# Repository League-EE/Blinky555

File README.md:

# League-EE-Blinky555

## Summary 

This project creates a circuit board with a flashing LED using a 555 timer IC.

This project spans for several sessions and will teach:

* Ohms Law and basic electronics
* How the 555 timer works
* Creating a schematic with Eagle
* Creating a printed circuit board with Eagle
* Soldering skills

## Eagle

See the section on [Eagle](Eagle/) for details.

## Lesson Plan

The [Lesson Plan](Lesson%20Plan/) folder has the formatted lesson plan

## LTspice

LTspice is a circuit simulator and can be incorporated into a future lesson. Simulation
files for the Blinky555 circuit are in the [LTSpice](LTSpice/) folder.

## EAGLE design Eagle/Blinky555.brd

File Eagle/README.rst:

*********************
League-EE-Blinky555
*********************

.. contents:: Table of Contents

Summary 
=========

These are the Eagle CAD files for the  555 timer, including schematic, board layout, and *most importantly, a custom Eagle library* so you don't have to go searching through thousands of parts.

.. figure:: Blinky555.png

Installation
====================

Install the Library
---------------------

This was the most confusing part. Eagle does not make it obvious at all how to add a library.

**(This needs to be updated!)**

1. Copy the *League_555_Blinky.lbr* file to the *lbr/* directory
2. Go to Library Manager and ???
3. Click on [Browse] button and navigate to the *League_555_Blinky.lbr* file
4. Click on Open

Copy the Project Files (Optional)
-----------------------------------

Create a folder where Eagle projects are stored. This is usually a different folder from the
program files.

Copy the .sch (schematic) and .brd (board file) into the new folder.

Laying Out
===========

Warning: Either the stop mask must be opened up underneath the coin cell or a solder blob
placed on the bottom pad to contact the bottom of the coin cell.

The example file includes a ground filled polygon.

Example Circuit
=================

**(Circuit not tested; the values were guessed at. Needs need updating.)**

.. figure:: Blinky555-schem.png

BOM (Bill of Materials)
========================

* Resistor, ?k, 0805, 2 pcs
* Capacitor, ?uF, 0805, 1 pc
* LED, 5 mm
* Timer IC, LM555
* Coin cell

  * CR1220 -- 12 mm diameter, 2 mm thick
  * CR2032 -- 20 mm diameter, 3.2 mm thick
  
* Coin cell holder, to match coin cell

  * CR1220 type -- Keystone, 3000
  * CR2032 type -- Linx Technologies, 712-BAT-HLD-001 

Recommended Reference Tutorials
================================

(Add links to best Eagle tutorials on the web; good for both instructors and kids as a reference.)

Ideas for Improvements
======================
* **Update the actual component values before ordering parts!**
* Add a potentiometer so the kids can adjust the blink rate
* Consider a speaker output and make this an oscillator/tone generator

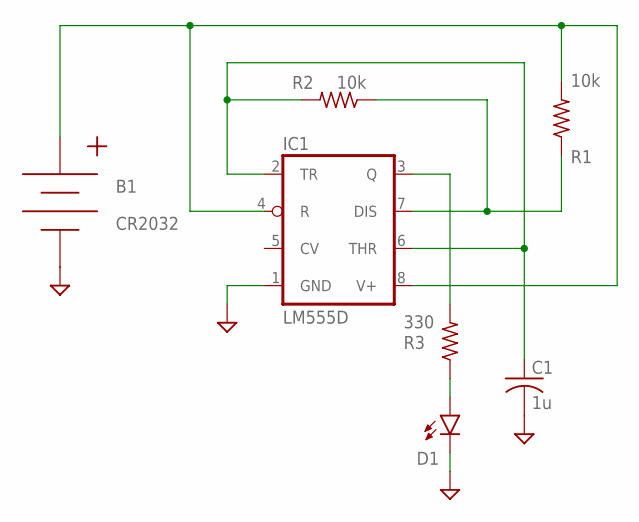
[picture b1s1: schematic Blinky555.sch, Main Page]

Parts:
B1: CR2032; BATTCON_20MM_4LEGS
C1: 1u; C0805
D1: LED; LED_5MM
IC1: LM555D; SO08
R1, R2: 10k; R0805
R3: 330; R0805

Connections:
+: B1.POSITIVE@1 (+), B1.POSITIVE@2 (+), B1.POSITIVE@3 (+), B1.POSITIVE@4 (+), IC1.4 (R), IC1.8 (V+), R1.2
GND: B1.NEGATIVE (-), C1.2, D1.K (C), IC1.1 (GND)
unnamed: IC1.7 (DIS), R1.1, R2.1
unnamed: C1.1, IC1.2 (TR), IC1.6 (THR), R2.2
unnamed: D1.A, R3.1
unnamed: IC1.3 (Q), R3.2

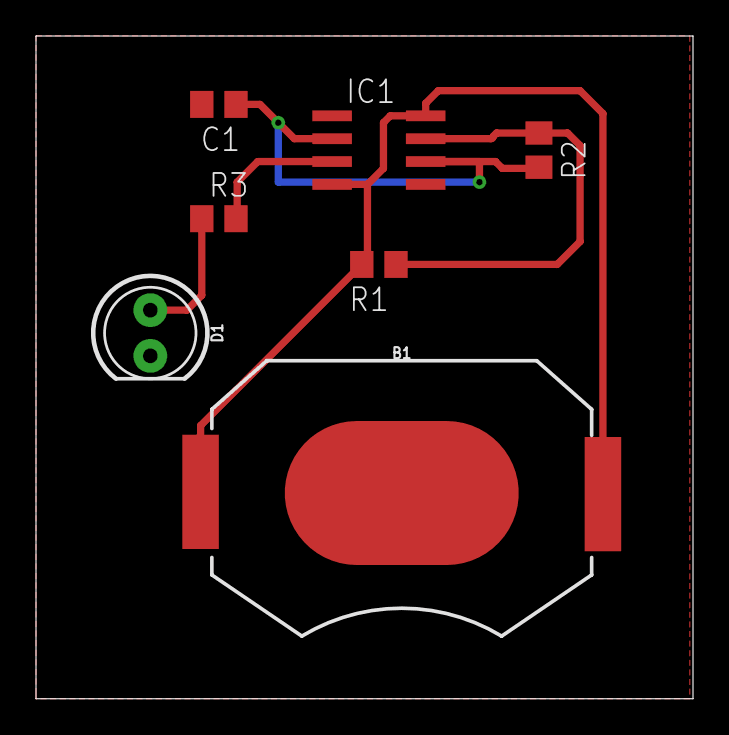
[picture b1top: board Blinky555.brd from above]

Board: 2 copper layers, 36.5 x 36.8 mm, 7 parts (0 on the bottom side), 6 nets.

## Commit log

2018-05-16 Added schematic image
